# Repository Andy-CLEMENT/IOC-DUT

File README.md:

# IOC-DUT — Repository Summary and Organization

This document serves as an entry point for navigating the [IOC-DUT](https://github.com/Andy-CLEMENT/IOC-DUT) repository, used as part of the internship at DNIIT (Da Nang) on the Intelligent Operation Center (IOC), carried out by Andy CLEMENT and Alexis MARTINI.

Internship planning: [Google Sheets](https://docs.google.com/spreadsheets/d/1JbVak5m1N3S0Dq-XeGyO9e7A00-PoN9cihRR5XMIRzQ/edit?gid=1161341563#gid=1161341563)

---

## Table of Contents

1. [Daily-Report](#1-daily-report) — daily reports
2. [Documents](#2-documents) — internship report and scientific papers
3. [Fire-Detection-IA](#3-fire-detection-ia) — fire/smoke detection AI model (the part Sadewa works on)
4. [Vietnamese-Code](#4-vietnamese-code) — legacy work from the Vietnamese team
5. [Root files](#5-root-files)
6. [System Deployment (Docker)](#6-system-deployment-docker)
7. [Quick Workflow Summary](#7-quick-workflow-summary)

---

## 1. Daily-Report

Daily reports written by each project member.

```
Daily-Report/
├── Alexis/
│   └── 020626.md
└── Andy/
    ├── report-06-03.md
    ├── report-06-15.md
    ├── report-06-17.md
    ├── report-06-23.md
    ├── report-06-31.md
    ├── report-07-10.md
    ├── report-07-21.md
    └── report-08-03.md
```

---

## 2. Documents

Official internship report and scientific bibliography used for the writing/research part.

```
Documents/
├── 30. DUT_Design and Development of an Intelligent Operation Center
│   (IOC) for Building Energy Management and Automated Control.pdf
└── Papers/          # 21 scientific papers (fire detection, deep
                      # learning, edge AI, building energy management...)
```

---

## 3. Fire-Detection-IA

Core of the camera-based fire and smoke detection project, deployed on the Jetson Orin Nano.

```
Fire-Detection-IA/
├── README.md                  # folder overview
├── To-Do.md                   # remaining tasks list
├── Overall_System_Design.png  # overall system diagram
├── yolo11m.pt                 # YOLO11m model weights
│
├── Data-Sheet/                # hardware datasheets (IP camera, Jetson Orin Nano)
│
├── Script-IA/                      # Python scripts running on the Jetson
│   ├── fire-detect-model.engine    # IA model compile for the jetson
│   ├── fire-detect.py              # main detection pipeline (GStreamer/RTSP → YOLO → WebSocket)
│   ├── serveur_relais.py           # relays data to the dashboard
│   └── run.sh                      # launches fire-detect.py and serveur_relais.py together (alias `fire-detect`)
│
├── training_model/            # training scripts for the different model versions
│   ├── trainV1.py … trainV4.py
│   └── train_resume.py
│
├── model_final/                # best model retained (best.pt)
│
├── predictions/                # prediction scripts and results on test images
│   ├── predict.py
│   └── test_after_training/
│
├── runs/detect/…                # raw Ultralytics training results
│   ├── yolov8s_fire_v1/         # YOLOv8s baseline (~84% accuracy)
│   ├── yolo11m_fire_v2/ … v4/   # YOLO11m model iterations
│       (PR/F1 curves, confusion matrices, best.pt/last.pt weights, etc.)
│
└── Test-screen/                # detection screenshots (fire/smoke)
```

> The `run.sh` script + the `fire-detect` alias (defined in `~/.bashrc` on the Jetson) let you launch the entire pipeline with a single command: `fire-detect`.

---

## 4. Vietnamese-Code

Previous work carried out by the Vietnamese team, reused and adapted for the internship.

```
Vietnamese-Code/
├── README.md
│
├── Alarm-System-Electronics/     # electronic alarm system (Arduino + PCB)
│   ├── Code/                     # .ino sketches (den_coi_final, nutnhan3, testgialapphantramkhoi)
│   └── PCB/                      # KiCad projects (Den_coi, Mach_bao_khoi, Nut_nhan_khan_cap)
│
├── New-Fire-Alarm/                # new version of the alarm system
│   ├── README.md
│   ├── fire-dashboard/            # React dashboard (Vite) — real-time alert visualization
│   ├── PCB/Mach_bao_khoi/         # PCB (Altium) for the alarm board
│   ├── main/main.ino
│   └── gui_thongtin_len_lorawan/  # sending data over LoRaWAN
│
├── FireAlarmApp-/                 # Expo/React Native mobile app
│
└── Wireless-Coverage-Prediction/  # ML pipeline for wireless network coverage prediction
    ├── README.md
    ├── data/                      # raw, processed, and terrain data (DEM, landuse)
    └── src/
        ├── api/                   # data retrieval
        ├── processing/            # cleaning, features, terrain
        └── ml/                    # training and prediction (XGBoost)
```

> **Dashboard**: launch it from `fire-dashboard/` with `npm install` (first time only), then `npm run dev` — works on Windows only. WebSocket address to enter: `ws://192.168.55.1:8765`.

---

## 5. Root files

| File                 | Description                                                                     |
| -------------------- | ------------------------------------------------------------------------------- |
| `README.md`        | General overview of the repository                                              |
| `Dockerfile`        | Container configuration for deploying the AI inference system                                              |
| `Running-Tutorial` | Getting-started tutorial: Jetson connection, headless VNC, Docker lunch         |
| `.gitignore`       | Files/folders excluded from Git tracking                                        |
| `docker-compose.yml`| Files for docker                                                               |
| `Dockerfile`       | Files for docker                                                                |

---

## 6. Quick Start

1. Connect to the Jetson via TightVNC to interact with graphic desktop (see `Running-Tutorial`). WARNING : Use a DATA USB cable to connect the Jetson (USB-C) to a USB port of your computer.
2. Connect to the Jetson with `IP : 192.168.55.1::5900` and `PWD : 987654321`
3. Go to the IOC-DUT directory in the Jetson (Currently is `~/repo/IOC-DUT`) Start the AI on the Jetson using the Docker container with `sudo docker compose up --build`.
4. Launch the dashboard on the PC or Jetson side (`IOC-DUT/Vietnamese-Code/New-Fire-Alarm/fire-dashboard`) with `setup-windows.ps1` or `setup-linux.sh` depending of your device.
5. Connect the dashboard to the Jetson via `ws://192.168.55.1:8765`

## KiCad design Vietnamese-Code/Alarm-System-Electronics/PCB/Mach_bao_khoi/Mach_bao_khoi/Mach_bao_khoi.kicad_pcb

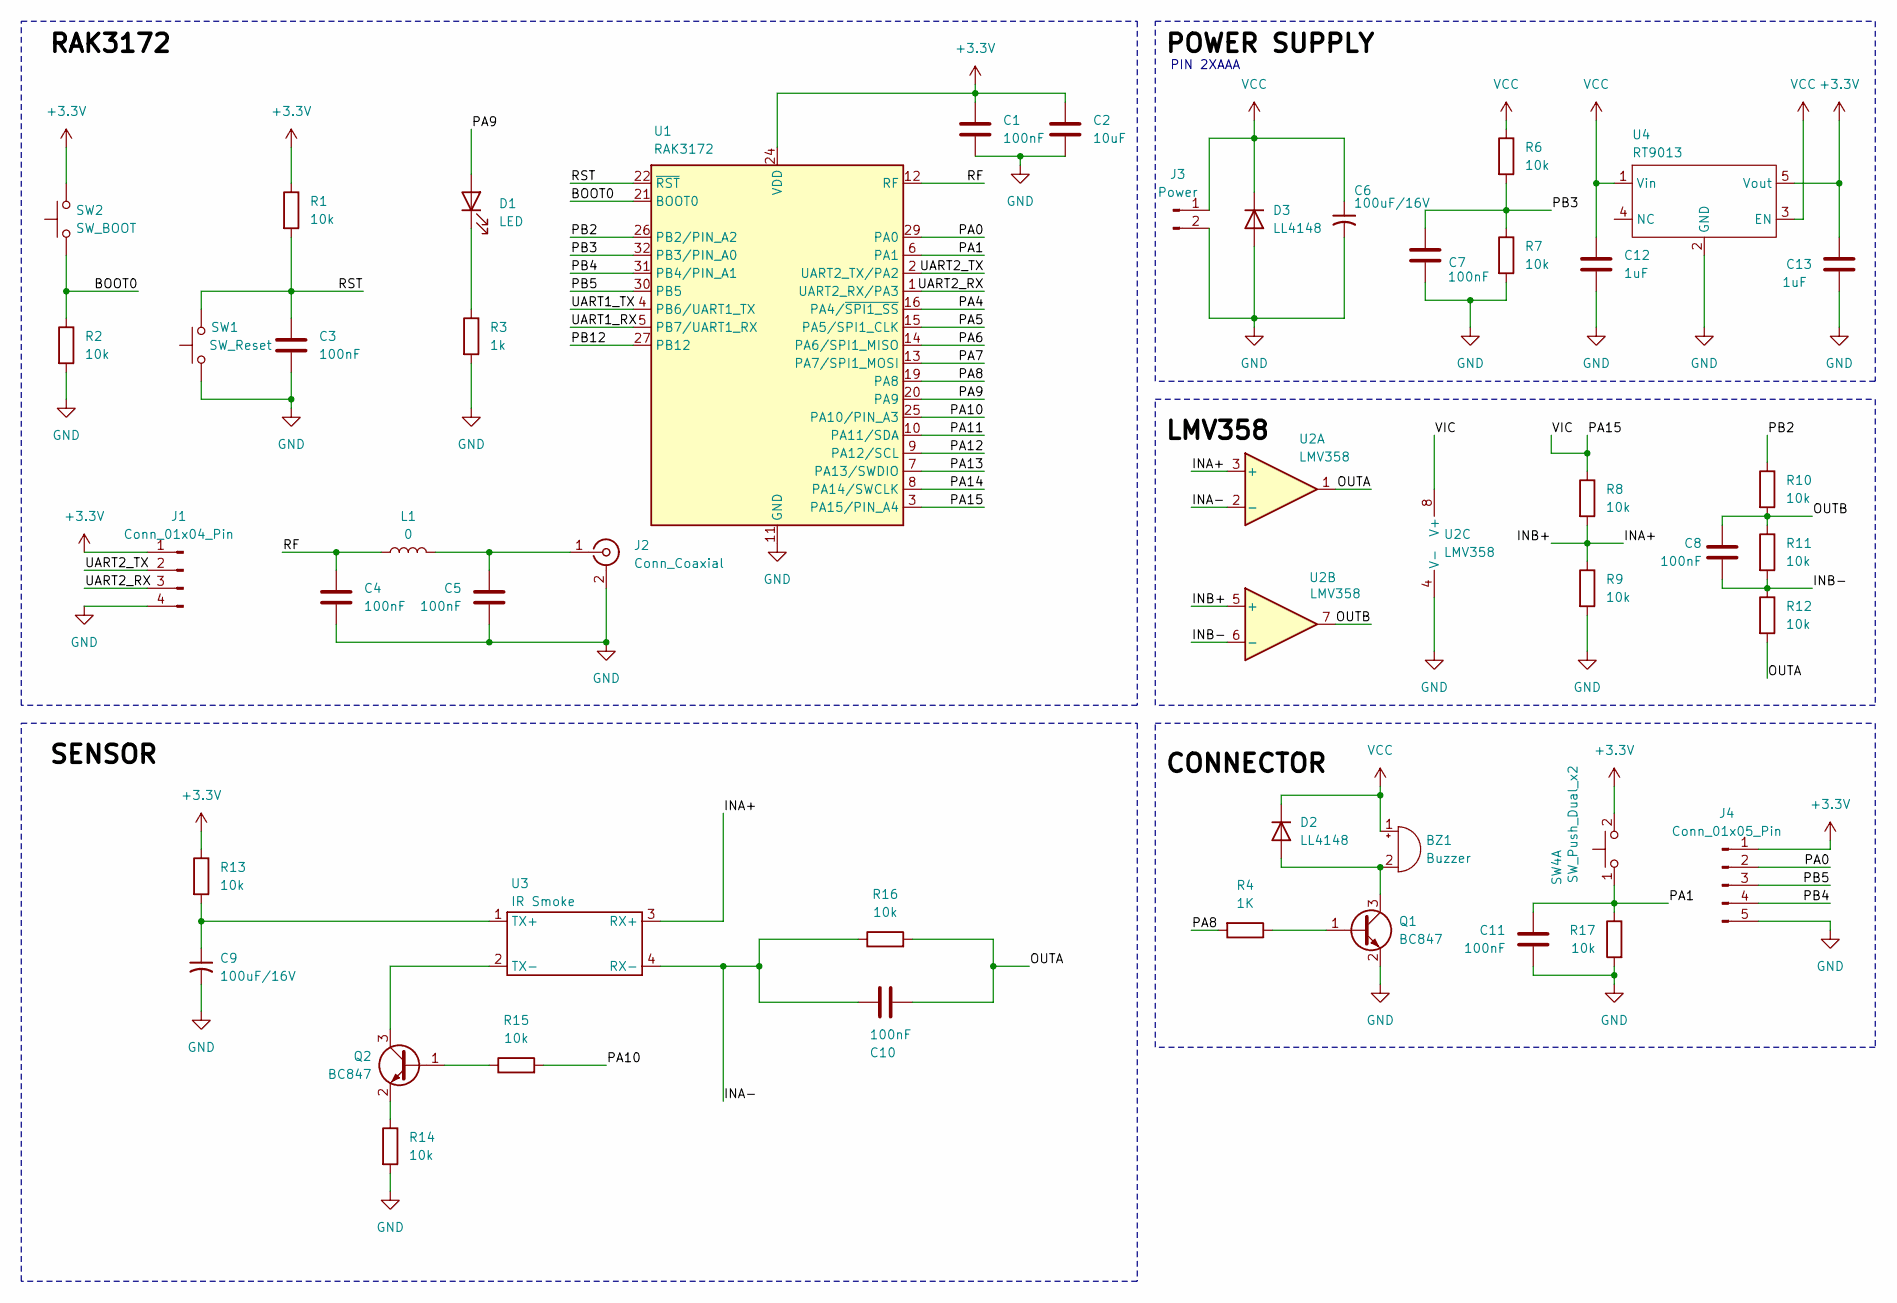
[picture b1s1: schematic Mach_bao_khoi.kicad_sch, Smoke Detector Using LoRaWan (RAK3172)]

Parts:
BZ1: Buzzer; Buzzer_CUI_CPT-9019S-SMT
C1, C3, C4, C5, C7, C8, C10, C11: 100nF; C_0603_1608Metric
C2: 10uF; C_0603_1608Metric
C6, C9: 100uF/16V; C_Elec_6.3x5.4
C12, C13: 1uF; C_0603_1608Metric
D1: LED; LED_0603_1608Metric
D2, D3: LL4148; D_MiniMELF
J1: Conn_01x04_Pin; PinHeader_1x04_P1.00mm_Horizontal
J2: Conn_Coaxial; U.FL_Molex_MCRF_73412-0110_Vertical
J3: Power; PinHeader_1x02_P1.27mm_Vertical
J4: Conn_01x05_Pin; PinHeader_1x05_P1.27mm_Vertical
L1: 0; L_0603_1608Metric
Q1, Q2: BC847; SOT-23
R1, R2, R6, R7, R8, R9, R10, R11, R12, R13, R14, R15, R16, R17: 10k; R_0603_1608Metric
R3: 1k; R_0603_1608Metric
R4: 1K; R_0603_1608Metric
SW1: SW_Reset; SW_SPST_B3U-1000P
SW2: SW_BOOT; SW_SPST_B3U-1000P
SW4: SW_Push_Dual_x2; SW_SPST_PTS645Sx43SMTR92
U1: RAK3172
U2: LMV358; SOIC-8_3.9x4.9mm_P1.27mm
U3: IR Smoke; Untitled_2
U4: RT9013; Untitled

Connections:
+3.3V: C1.1, C2.1, C13.1, J1.1, J4.1, R1.1, R13.1, SW2.2, SW4.2 (D), U1.24 (VDD), U4.5 (Vout)
/<NO NET>: C8.2, R11.2, R12.1, U2.6 (-)
/BOOT0: R2.1, SW2.1, U1.21 (BOOT0)
/INA+: R8.2, R9.1, U2.3 (+), U2.5 (+), U3.3 (RX+)
/INA-: C10.1, R16.1, U2.2 (-), U3.4 (RX-)
/OUTA: C10.2, R12.2, R16.2, U2.1
/OUTB: C8.1, R10.2, R11.1, U2.7
/PA0: J4.2, U1.29 (PA0)
/PA1: C11.1, R17.1, SW4.1 (C), U1.6 (PA1)
/PA4: U1.16 (PA4/~SPI1_SS)
/PA5: U1.15 (PA5/SPI1_CLK)
/PA6: U1.14 (PA6/SPI1_MISO)
/PA7: U1.13 (PA7/SPI1_MOSI)
/PA8: R4.2, U1.19 (PA8)
/PA9: D1.2 (A), U1.20 (PA9)
/PA10: R15.2, U1.25 (PA10/PIN_A3)
/PA11: U1.10 (PA11/SDA)
/PA12: U1.9 (PA12/SCL)
/PA13: U1.7 (PA13/SWDIO)
/PA14: U1.8 (PA14/SWCLK)
/PA15: R8.1, U1.3 (PA15/PIN_A4), U2.8 (V+)
/PB2: R10.1, U1.26 (PB2/PIN_A2)
/PB3: C7.1, R6.2, R7.1, U1.32 (PB3/PIN_A0)
/PB4: J4.4, U1.31 (PB4/PIN_A1)
/PB5: J4.3, U1.30 (PB5)
/PB12: U1.27 (PB12)
/RF: C4.1, L1.1, U1.12 (RF)
/RST: C3.1, R1.2, SW1.2, U1.22 (~RST)
/UART1_RX: U1.5 (PB7/UART1_RX)
/UART1_TX: U1.4 (PB6/UART1_TX)
/UART2_RX: J1.3, U1.1 (UART2_RX/PA3)
/UART2_TX: J1.2, U1.2 (UART2_TX/PA2)
GND: C1.2, C2.2, C3.2, C4.2, C5.2, C6.2, C7.2, C9.2, C11.2, C12.2, C13.2, D3.2 (A), J1.4, J2.2 (Ext), J3.2, J4.5, Q1.2 (E), R2.2, R3.2, R7.2, R9.2, R14.2, R17.2, SW1.1, U1.11 (GND), U1.17 (GND), U1.18 (GND), U1.23 (GND), U1.28 (GND), U2.4 (V-), U4.2 (GND)
unnamed: BZ1.2 (-), D2.2 (A), Q1.3 (C)
unnamed: D1.1 (K), R3.1
unnamed: C5.1, J2.1 (In), L1.2
unnamed: Q1.1 (B), R4.1
unnamed: Q2.1 (B), R15.1
unnamed: Q2.3 (C), U3.2 (TX-)
unnamed: Q2.2 (E), R14.1
unnamed: C9.1, R13.2, U3.1 (TX+)
VCC: BZ1.1 (+), C6.1, C12.1, D2.1 (K), D3.1 (K), J3.1, R6.1, U4.1 (Vin), U4.3 (EN)

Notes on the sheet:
PIN 2XAAA

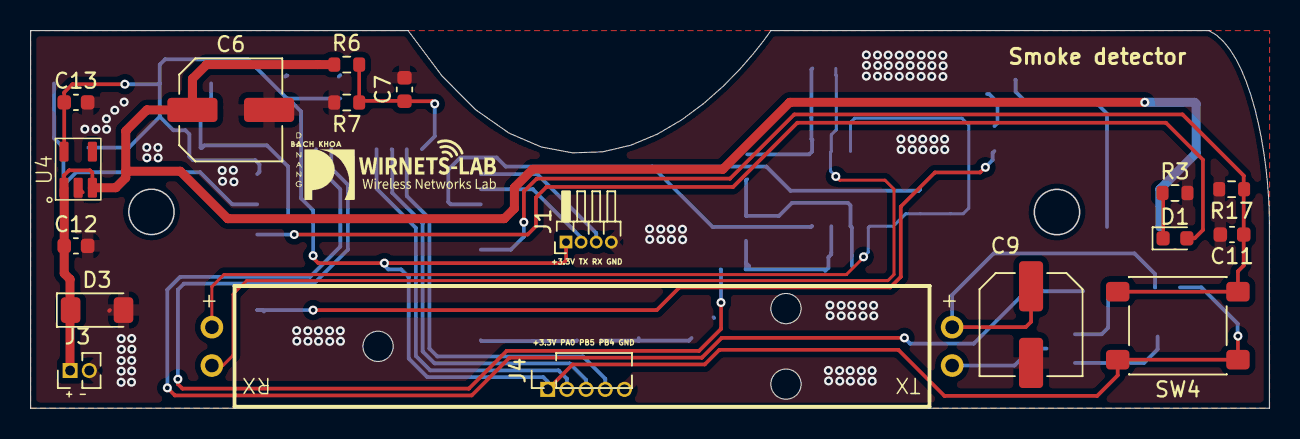
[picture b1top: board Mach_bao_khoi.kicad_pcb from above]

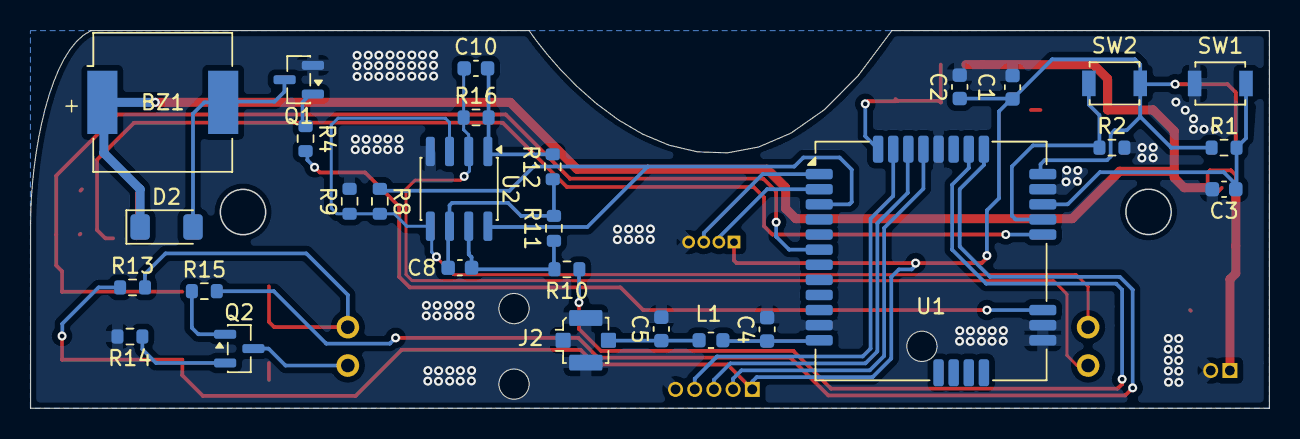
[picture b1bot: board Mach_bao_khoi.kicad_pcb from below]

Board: 2 copper layers, 82.0 x 25.0 mm, 47 parts (29 on the bottom side), 31 nets.

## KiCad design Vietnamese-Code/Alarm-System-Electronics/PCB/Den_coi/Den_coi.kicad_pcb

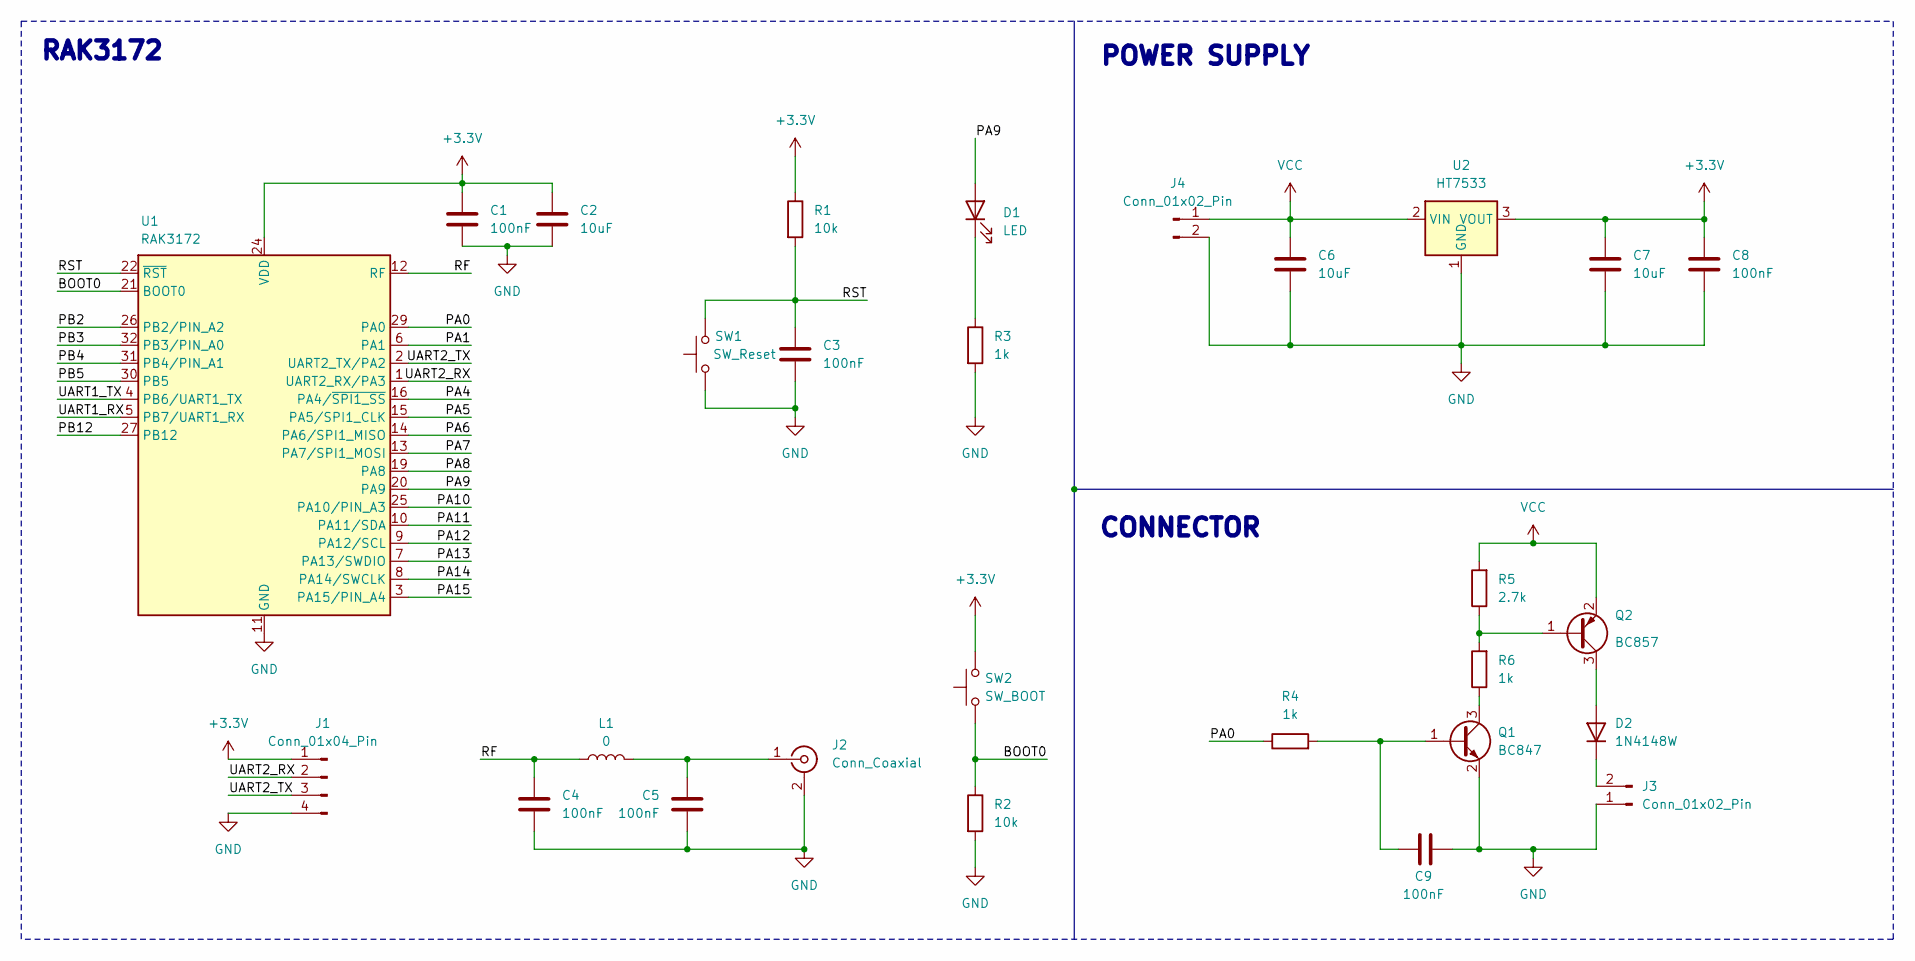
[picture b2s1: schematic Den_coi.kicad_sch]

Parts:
C1, C3, C4, C5, C8, C9: 100nF; C_0603_1608Metric
C2, C6, C7: 10uF; C_0603_1608Metric
D1: LED; LED_0603_1608Metric
D2: 1N4148W; D_SOD-123
J1: Conn_01x04_Pin; PinHeader_1x04_P1.00mm_Horizontal
J2: Conn_Coaxial; U.FL_Molex_MCRF_73412-0110_Vertical
J3: Conn_01x02_Pin; PinHeader_1x02_P1.00mm_Vertical
J4: Conn_01x02_Pin; PinHeader_1x02_P2.00mm_Vertical
L1: 0; L_0603_1608Metric
Q1: BC847; SOT-23
Q2: BC857; SOT-23
R1, R2: 10k; R_0603_1608Metric
R3, R4, R6: 1k; R_0603_1608Metric
R5: 2.7k; R_0603_1608Metric
SW1: SW_Reset; SW_SPST_B3U-1000P
SW2: SW_BOOT; SW_SPST_B3U-1000P
U1: RAK3172
U2: HT7533; SOT-89-3

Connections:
+3.3V: C1.1, C2.1, C7.1, C8.1, J1.1, R1.1, SW2.2, U1.24 (VDD), U2.3 (VOUT)
/BOOT0: R2.1, SW2.1, U1.21 (BOOT0)
/PA0: R4.1, U1.29 (PA0)
/PA1: U1.6 (PA1)
/PA4: U1.16 (PA4/~SPI1_SS)
/PA5: U1.15 (PA5/SPI1_CLK)
/PA6: U1.14 (PA6/SPI1_MISO)
/PA7: U1.13 (PA7/SPI1_MOSI)
/PA8: U1.19 (PA8)
/PA9: D1.2 (A), U1.20 (PA9)
/PA10: U1.25 (PA10/PIN_A3)
/PA11: U1.10 (PA11/SDA)
/PA12: U1.9 (PA12/SCL)
/PA13: U1.7 (PA13/SWDIO)
/PA14: U1.8 (PA14/SWCLK)
/PA15: U1.3 (PA15/PIN_A4)
/PB2: U1.26 (PB2/PIN_A2)
/PB3: U1.32 (PB3/PIN_A0)
/PB4: U1.31 (PB4/PIN_A1)
/PB5: U1.30 (PB5)
/PB12: U1.27 (PB12)
/RF: C4.1, L1.1, U1.12 (RF)
/RST: C3.1, R1.2, SW1.2, U1.22 (~RST)
/UART1_RX: U1.5 (PB7/UART1_RX)
/UART1_TX: U1.4 (PB6/UART1_TX)
/UART2_RX: J1.2, U1.1 (UART2_RX/PA3)
/UART2_TX: J1.3, U1.2 (UART2_TX/PA2)
GND: C1.2, C2.2, C3.2, C4.2, C5.2, C6.2, C7.2, C8.2, C9.1, J1.4, J2.2 (Ext), J3.1, J4.2, Q1.2 (E), R2.2, R3.2, SW1.1, U1.11 (GND), U1.17 (GND), U1.18 (GND), U1.23 (GND), U1.28 (GND), U2.1 (GND)
unnamed: D1.1 (K), R3.1
unnamed: D2.2 (A), Q2.3 (C)
unnamed: D2.1 (K), J3.2
unnamed: C5.1, J2.1 (In), L1.2
unnamed: C9.2, Q1.1 (B), R4.2
unnamed: Q1.3 (C), R6.1
unnamed: Q2.1 (B), R5.1, R6.2
VCC: C6.1, J4.1, Q2.2 (E), R5.2, U2.2 (VIN)

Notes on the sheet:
CONNECTOR
RAK3172
POWER SUPPLY

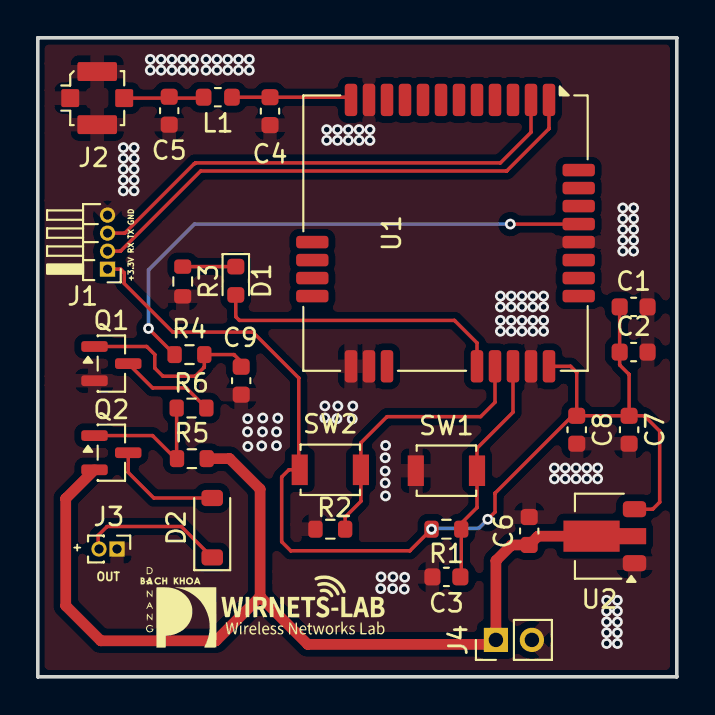
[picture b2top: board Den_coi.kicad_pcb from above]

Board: 2 copper layers, 35.5 x 35.5 mm, 28 parts (0 on the bottom side), 17 nets.

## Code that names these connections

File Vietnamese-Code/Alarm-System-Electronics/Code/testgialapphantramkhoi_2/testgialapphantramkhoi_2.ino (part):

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// ============================================================
//  SƠ ĐỒ CHÂN
// ============================================================
#define SMOKE_ADC_PIN       PB2    // Output LMV258 tầng 2 → ADC MCU
#define IR_LED_CTRL_PIN     PA10   // HIGH → transistor NPN dẫn → LED IR sáng
#define LMV258_POWER_PIN    PA15   // HIGH → cấp nguồn LMV258
#define BUZZER_PIN          PA8    // Còi báo động (PWM non-blocking)
#define STATUS_LED_PIN      PA9    // LED trạng thái  
#define TEST_BUTTON_PIN     PA1    // Nút nhấn test / im lặng

// ============================================================
//  LORAWAN OTAA KEYS — điền đúng trước khi deploy
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  analogReadResolution(12);

  // -------------------------------------------------------
  //  Tăng drive strength PA8 (BUZZER) lên mức tối đa
  //  STM32WLE5: OSPEEDR = 11 (Very High), OTYPER = 0 (Push-Pull)
  //  → Tăng dòng kéo còi piezo, tiếng to hơn đáng kể
  // -------------------------------------------------------
  GPIOA->OTYPER  &= ~(1U << 8);          // Push-Pull (không open-drain)
  GPIOA->OSPEEDR |=  (3U << (8 * 2));    // Very High Speed trên PA8

  irLedOff(); lmv258Off(); buzzerStop(); ledOff();
}
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  pinMode(SMOKE_ADC_PIN,    INPUT);
  analogReadResolution(12);

  // Khôi phục drive strength PA8 sau khi wake (sleep có thể reset)
  GPIOA->OTYPER  &= ~(1U << 8);
  GPIOA->OSPEEDR |=  (3U << (8 * 2));

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
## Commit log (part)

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2026-05-20 ajouts docs de base
2026-05-20 test
2026-05-20 All data
2026-05-20 ajout code
2026-05-20 Note-Article update
2026-05-20 ajout petit texte limites article
2026-05-20 Note articles update
2026-05-21 Update Note-Article
2026-05-22 rename dossier
2026-05-22 Update Note Alarme
2026-05-22 Add LoRa code for device
2026-05-25 ajout docs
2026-05-28 Reorganisation of the repo
2026-05-29 Datasheet and equipment
2026-06-01 To-Do
2026-06-02 Daily-report-upadte
2026-06-02 debut entrainement ia 23 epoch
2026-06-02 clean and add resume python
2026-06-02 deplacement bon dossier
2026-06-02 second training
2026-06-02 clean training
2026-06-02 training finish
2026-06-03 finalisation ia
2026-06-03 IA-detector
2026-06-03 ajout gitignore
2026-06-03 gitignore
2026-06-03 maj fire-detec
2026-06-03 ajout websocket communication 1
2026-06-03 report and fire-detect.py
2026-06-15 clean fire-detec.py
2026-06-15 Report
2026-06-17 New version of python script
2026-06-17 fichier server
2026-06-17 fix firedetect.py
2026-06-17 fix smoke et online fire_detect
2026-06-17 ajout run all
2026-06-17 Fire-detect rework
2026-06-22 MAJ report
2026-06-23 New version of fire-detect.py
2026-06-29 add trainings
2026-06-29 update dayly report
2026-06-30 Update repo
